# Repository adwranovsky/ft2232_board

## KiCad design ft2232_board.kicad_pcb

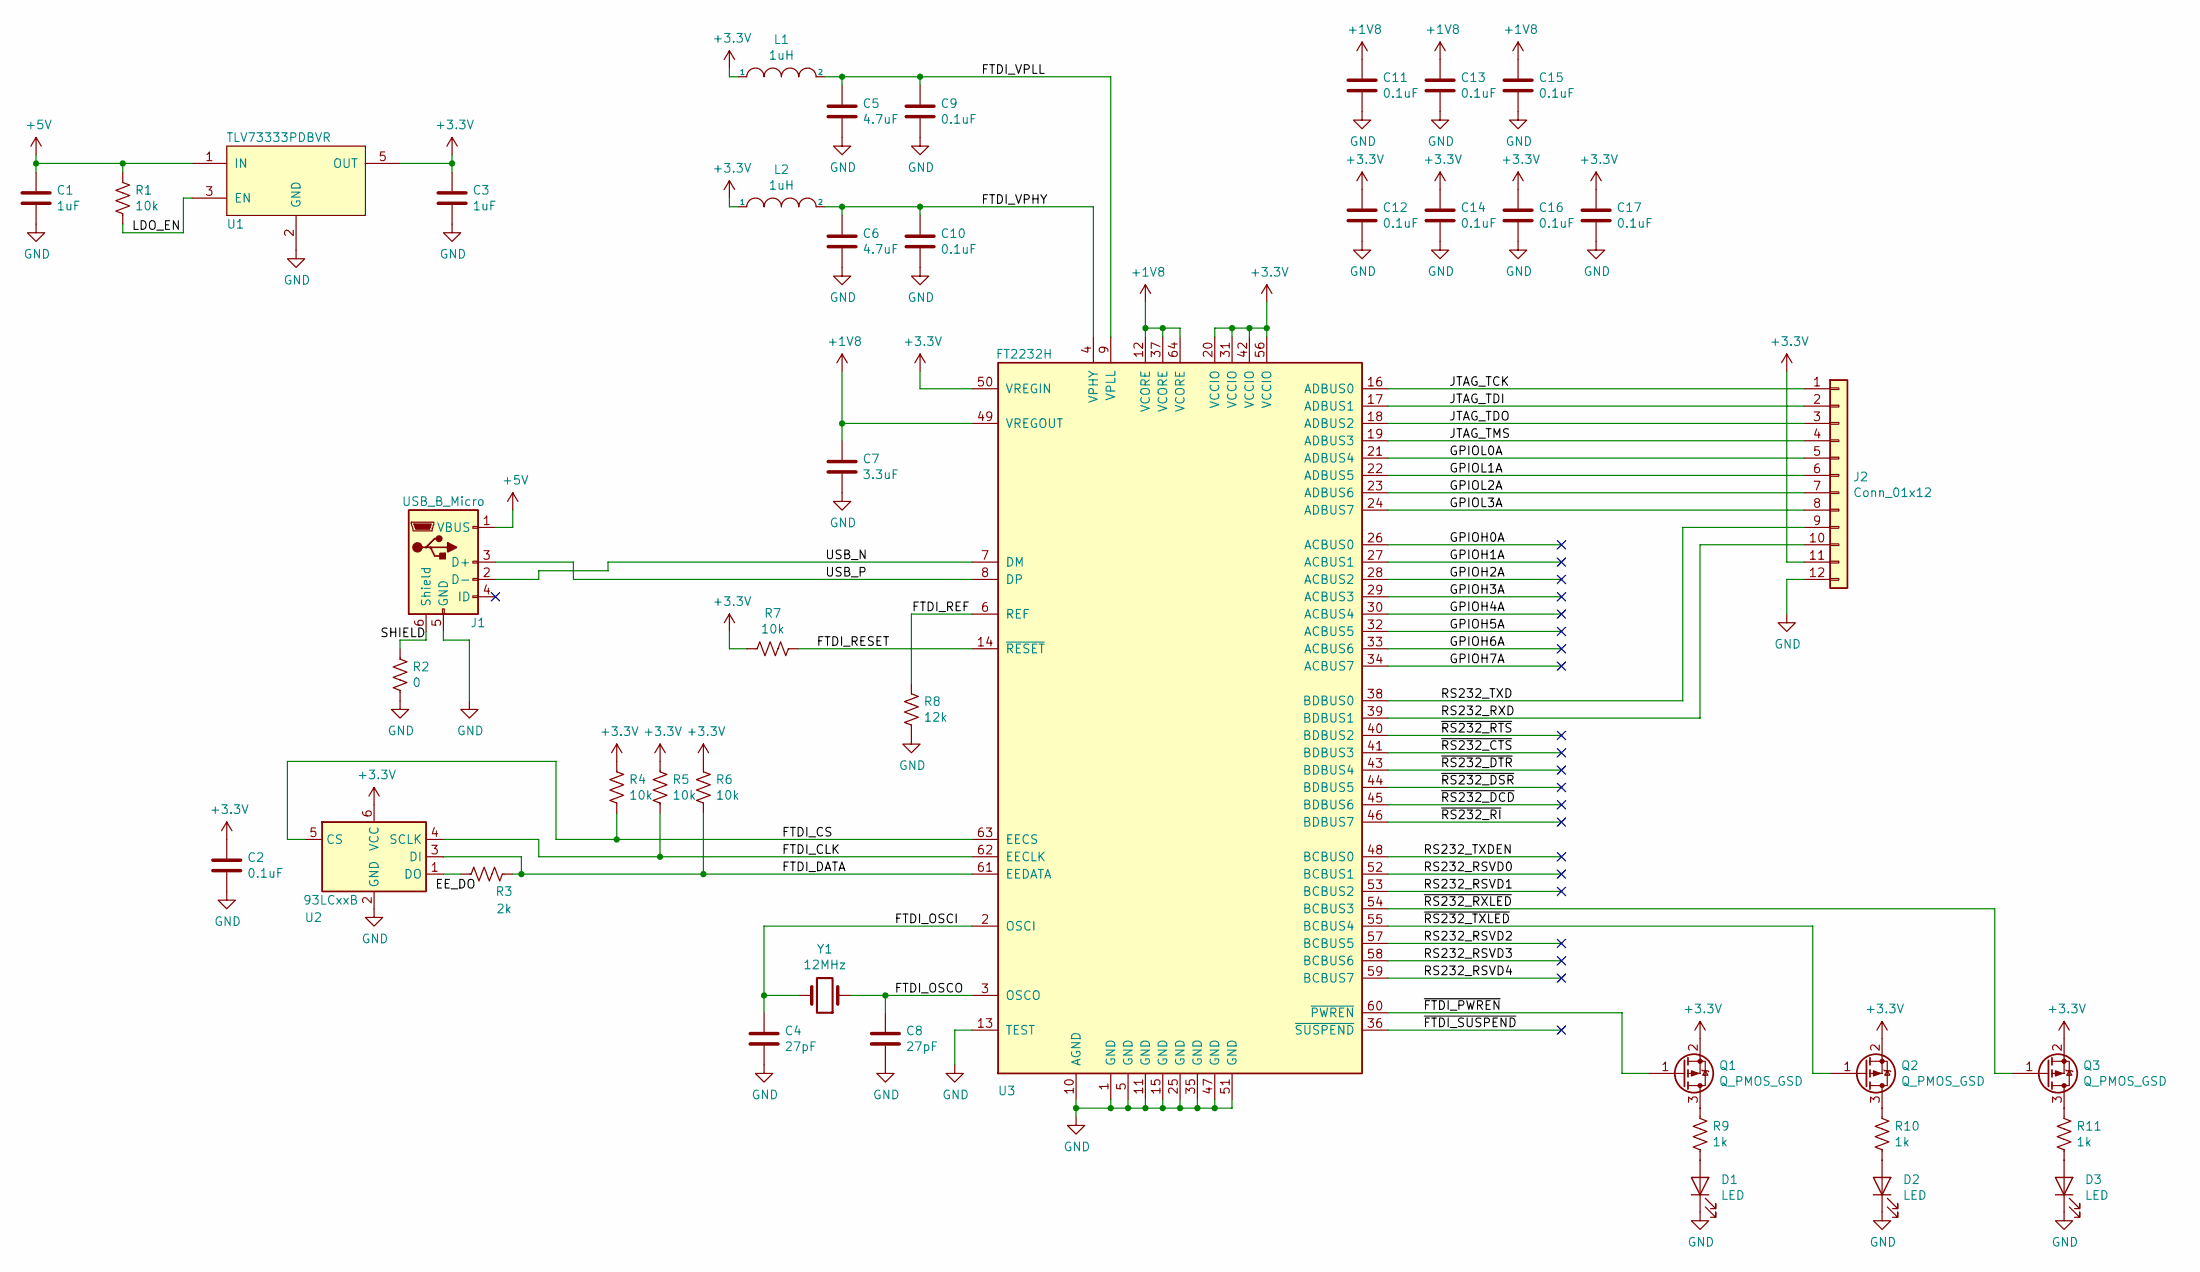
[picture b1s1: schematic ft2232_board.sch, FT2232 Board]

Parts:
C1, C3: 1uF; C_0805_2012Metric
C2, C9, C10, C11, C12, C13, C14, C15, C16, C17: 0.1uF; C_0805_2012Metric
C4, C8: 27pF; C_0805_2012Metric
C5, C6: 4.7uF; C_0805_2012Metric
C7: 3.3uF; C_0805_2012Metric
D1, D2, D3: LED; LED_0402_1005Metric
J1: USB_B_Micro; USB_Micro_B_10118194-0X0XLF
J2: Conn_01x12; PinHeader_1x12_P2.54mm_Vertical
L1, L2: 1uH; L_0805_2012Metric
Q1, Q2, Q3: Q_PMOS_GSD; SOT-23
R1, R4, R5, R6, R7: 10k; R_0805_2012Metric
R2: 0; R_0805_2012Metric
R3: 2k; R_0805_2012Metric
R8: 12k; R_0805_2012Metric
R9, R10, R11: 1k; R_0805_2012Metric
U1: TLV73333PDBVR; SOT-23-5_HandSoldering
U2: 93LCxxB; SOT-23-6_Handsoldering
U3: FT2232H; LQFP-64_10x10mm_P0.5mm
Y1: 12MHz; Crystal_SMD_HC49-SD_HandSoldering

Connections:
+1V8: C7.1, C11.1, C13.1, C15.1, U3.12 (VCORE), U3.37 (VCORE), U3.49 (VREGOUT), U3.64 (VCORE)
+3V3: C2.1, C3.1, C12.1, C14.1, C16.1, C17.1, J2.11, L1.1, L2.1, Q1.2 (S), Q2.2 (S), Q3.2 (S), R4.2, R5.2, R6.2, R7.2, U1.5 (OUT), U2.6 (VCC), U3.20 (VCCIO), U3.31 (VCCIO), U3.42 (VCCIO), U3.50 (VREGIN), U3.56 (VCCIO)
+5V: C1.1, J1.1 (VBUS), R1.1, U1.1 (IN)
/FTDI_CLK: R5.1, U2.4 (SCLK), U3.62 (EECLK)
/FTDI_CS: R4.1, U2.5 (CS), U3.63 (EECS)
/FTDI_DATA: R3.1, R6.1, U2.3 (DI), U3.61 (EEDATA)
/FTDI_OSCI: C4.1, U3.2 (OSCI), Y1.2
/FTDI_OSCO: C8.1, U3.3 (OSCO), Y1.1
/FTDI_REF: R8.2, U3.6 (REF)
/FTDI_RESET: R7.1, U3.14 (~RESET)
/FTDI_VPHY: C6.1, C10.1, L2.2, U3.4 (VPHY)
/FTDI_VPLL: C5.1, C9.1, L1.2, U3.9 (VPLL)
/GPIOH0A: U3.26 (ACBUS0)
/GPIOH1A: U3.27 (ACBUS1)
/GPIOH2A: U3.28 (ACBUS2)
/GPIOH3A: U3.29 (ACBUS3)
/GPIOH4A: U3.30 (ACBUS4)
/GPIOH5A: U3.32 (ACBUS5)
/GPIOH6A: U3.33 (ACBUS6)
/GPIOH7A: U3.34 (ACBUS7)
/GPIOL0A: J2.5, U3.21 (ADBUS4)
/GPIOL1A: J2.6, U3.22 (ADBUS5)
/GPIOL2A: J2.7, U3.23 (ADBUS6)
/GPIOL3A: J2.8, U3.24 (ADBUS7)
/JTAG_TCK: J2.1, U3.16 (ADBUS0)
/JTAG_TDI: J2.2, U3.17 (ADBUS1)
/JTAG_TDO: J2.3, U3.18 (ADBUS2)
/JTAG_TMS: J2.4, U3.19 (ADBUS3)
/LDO_EN: R1.2, U1.3 (EN)
/RS232_RSVD0: U3.52 (BCBUS1)
/RS232_RSVD1: U3.53 (BCBUS2)
/RS232_RSVD2: U3.57 (BCBUS5)
/RS232_RSVD3: U3.58 (BCBUS6)
/RS232_RSVD4: U3.59 (BCBUS7)
/RS232_RXD: J2.10, U3.39 (BDBUS1)
/RS232_TXD: J2.9, U3.38 (BDBUS0)
/RS232_TXDEN: U3.48 (BCBUS0)
/SHIELD: J1.6 (Shield), R2.2
/USB_N: J1.2 (D-), U3.7 (DM)
/USB_P: J1.3 (D+), U3.8 (DP)
/~FTDI_PWREN~: Q1.1 (G), U3.60 (~PWREN)
/~FTDI_SUSPEND~: U3.36 (~SUSPEND)
/~RS232_CTS~: U3.41 (BDBUS3)
/~RS232_DCD~: U3.45 (BDBUS6)
/~RS232_DSR~: U3.44 (BDBUS5)
/~RS232_DTR~: U3.43 (BDBUS4)
/~RS232_RI~: U3.46 (BDBUS7)
/~RS232_RTS~: U3.40 (BDBUS2)
/~RS232_RXLED~: Q3.1 (G), U3.54 (BCBUS3)
/~RS232_TXLED~: Q2.1 (G), U3.55 (BCBUS4)
GND: C1.2, C2.2, C3.2, C4.2, C5.2, C6.2, C7.2, C8.2, C9.2, C10.2, C11.2, C12.2, C13.2, C14.2, C15.2, C16.2, C17.2, D1.1 (K), D2.1 (K), D3.1 (K), J1.5 (GND), J2.12, R2.1, R8.1, U1.2 (GND), U2.2 (GND), U3.1 (GND), U3.5 (GND), U3.10 (AGND), U3.11 (GND), U3.13 (TEST), U3.15 (GND), U3.25 (GND), U3.35 (GND), U3.47 (GND), U3.51 (GND)
unnamed: D1.2 (A), R9.2
unnamed: D2.2 (A), R10.2
unnamed: D3.2 (A), R11.2
unnamed: Q1.3 (D), R9.1
unnamed: Q2.3 (D), R10.1
unnamed: Q3.3 (D), R11.1
unnamed: R3.2, U2.1 (DO)

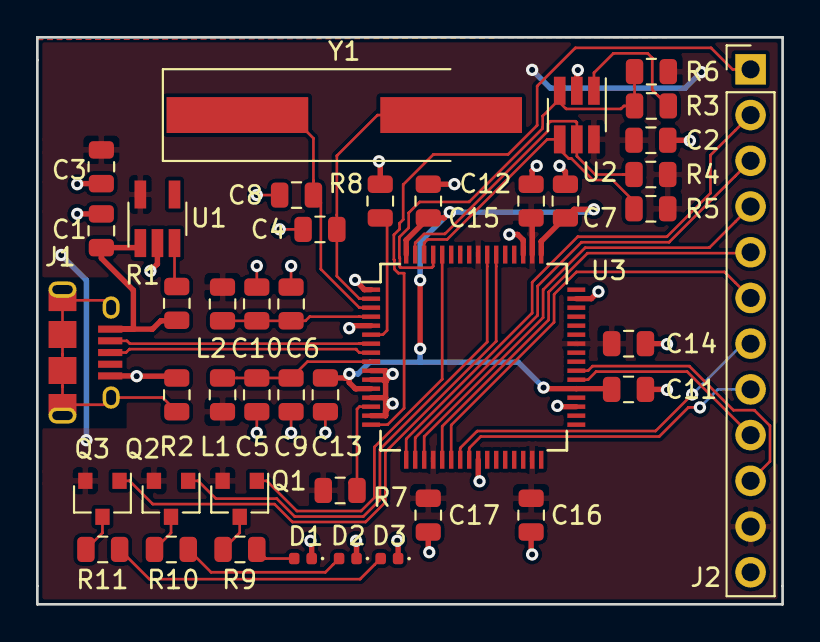
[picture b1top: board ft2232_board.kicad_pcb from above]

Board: 2 copper layers, 41.4 x 31.5 mm, 42 parts (0 on the bottom side), 37 nets.

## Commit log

2019-11-26 Initial commit with completed rev A schematic and PCB.
